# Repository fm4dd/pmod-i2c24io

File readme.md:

## PMOD-I2C24IO

### Description

This project is a 24-bit digital IO expander module, using the Texas Instruments TCA6424A circuit utilizing I2C. The design is available with two connector types: either Type-6 (I2C single-row) or Type-6A (I2C extended double-row) compatible interface per open PMOD interface standard v1.3.1 by Digilent Inc. PMOD (peripheral module interface) standardizes connectivity with FPGA or microcontroller development boards.
This design is registered under the OSHWA Open Source Hardware Self-Certification:  

### Function
In this module, 24 IO pins are controlled through the two-wire serial I2C protocol. For each individual IO pin, a corresponding LED displays its current status with negative logic. A pins logic level '0' lights up the LED, while level '1' turns it off. To fit all IO pins on a reasonably small PMOD, 0402-size SMD components have been selected. DIP switches enable I2C pull-up resistors if needed, and change the I2C bus address between 0x22 and 0x23. Two modules can be chained for a total of 48 IO signals. Three Testpoints can be fitted for I2C bus troubleshooting.  

See also http://fpga.fm4dd.com/

### Schematic

Type-6 v1.1 variant:

Type-6 Physical Dimensions: 60 mm x 20.3 mm

### Hardware Release

|Type     | Version | Gerber | Schema |
|---------|---------|--------|--------|
|Type-6   | 1.0     |[20210906-pmod-i2c24io-t6-gerber-v10.zip](release/t6-v10/20210906-pmod-i2c24io-t6-gerber-v10.zip) | [20210906-pmod-i2c24io-t6-schema-v10.pdf](images/t6-v11/20210906-pmod-i2c24io-t6-schema-v10.pdf) |
|Type-6   |1.1      |[20210919-pmod-i2c24io-t6-gerber-v11.zip](release/t6-v11/20210919-pmod-i2c24io-t6-gerber-v11.zip) | [20210919-pmod-i2c24io-t6-schema-v11.pdf](release/t6-v11/20210919-pmod-i2c24io-t6-schema-v11.pdf)
|Type-6A  |1.1      |[20210919-pmod-i2c24io-t6a-gerber-v11.zip](release/t6a-v11/20210919-pmod-i2c24io-t6a-gerber-v11.zip) | [20210919-pmod-i2c24io-t6a-schema-v11.pdf](release/t6a-v11/20210919-pmod-i2c24io-t6a-schema-v11.pdf)

Type-6A v1.1 variant:

Type-6A Physical Dimensions: 62.5 mm x 21.7 mm

### Module Pin Assignments

Type 6:
| Pin | Signal | Description |
|-----|--------|-------------|
| 1   | Reset  | TCA6424A Reset Pin |
| 2   | Int    | TCA6424A Interrupt Pin |
| 3   | SCL    | I2C Clock Signal |
| 4   | SDA    | I2C Data Signal |
| 5   | GND    | Power Supply Ground |
| 6   | VCC    | Power Supply (3.3V) |

Type 6A (Pin 1-6 same as Type 6)

| Pin | Signal | Description |
|-----|--------|-------------|
| 7   | IO1    | IO signal 1 |
| 8   | IO2    | IO signal 2 |
| 9   | IO3    | IO signal 3 |
| 10  | IO4    | IO signal 4 |
| 11  | GND    | Power Supply Ground |
| 12  | VCC    | Power Supply (3.3V) |

Note: all pin signals are passed from the module pin header to the opposite pin socket, allowing to chain another I2C module to the I2C bus.

#### Rasperry Pi I2C Discovery

First we set Reset pin 'high' to enable circuit operation by exiting the reset state. The gpioset command here is part of the 'gpiod' pin control program and library, installed with 'sudo apt install gpiod'.
```
pi@pi-ms05:~/pmod2rpi/pi-tca6424a $ gpioset gpiochip0 22=1
```
Now we can see the IO expander circuit under address 0x22 (address pin = '1'), or 0x23 (address pin = '0').
```
pi@pi-ms05:~/pmod2rpi/pi-tca6424a $ i2cdetect -y 1
     0  1  2  3  4  5  6  7  8  9  a  b  c  d  e  f
00:          -- -- -- -- -- -- -- -- -- -- -- -- --
10: -- -- -- -- -- -- -- -- -- -- -- -- -- -- -- --
20: -- -- 22 -- -- -- -- -- -- -- -- -- -- -- -- --
...
```

Note: From I2C24IO module hardware version 1.1, two additional 10K pull-up resistors (R28,29) have been fitted to auto-enable the circuit, which eliminates the need to explicitly configure the 'Reset' pin.

### Example Code

| Platform | Folder | Description |
|----------|--------|-------------|
|Raspberry Pi |[pi-tca6424a](examples/pi-tca6424a)   | I2C module driver 'C' program to control the expander 24 IO output pins individually, and as a set |
|Arduino      |[xiao-pmod1-i2c24io](examples/xiao-pmod1-i2c24io)   | Tests I2C ports 0x22 and 0x23. If a module is found, all IO pins are set as 'output=0' (lighting up all LED) |
|Arduino      |[xiao-pmod1-24iodemo](examples/xiao-pmod1-24iodemo)   | Creates a lightshow demo by rotating binary patterns over the 24 IO pins, lighting up connected LEDs |

Two I2C24IO PMOD's connected to the RPi PMOD Interface board connector PMOD1 and PMOD2, running the "xiao-double-i2c24io" example program on the Seeeduino XIAO (Cortex M0):

I2C24IO PMOD connected to the RPi PMOD Interface board connector PMOD4, running the "demotca6424a" example program on the Raspberry Pi:

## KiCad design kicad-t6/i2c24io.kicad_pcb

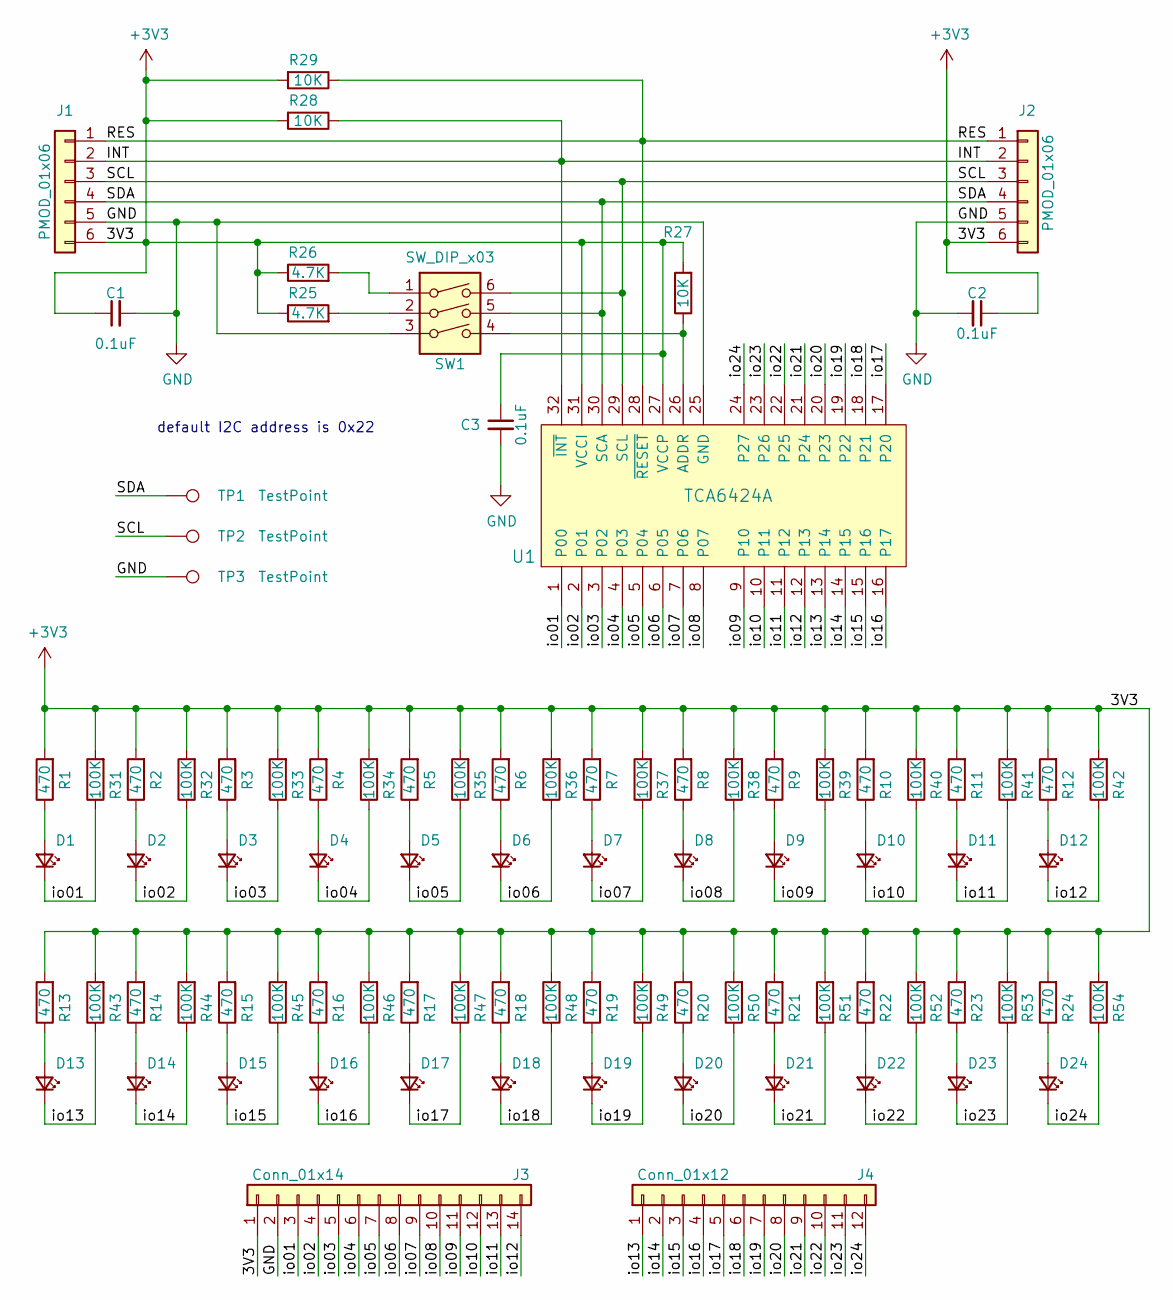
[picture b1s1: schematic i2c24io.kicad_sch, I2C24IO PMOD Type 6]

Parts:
C1, C2, C3: 0.1uF; C_0402_1005Metric
D1, D2, D3, D4, D5, D6, D7, D8, D9, D10, D11, D12, D13, D14, D15, D16, D17, D18, D19, D20, D21, D22, D23, D24: LED_Small; LED_0402_1005Metric
J1: PMOD_01x06; PMOD_Header_1x06_P2.54mm_Horizontal
J2: PMOD_01x06; PMODPinSocket_1x06_P2.54mm_Horizontal
J3: Conn_01x14; PinHeader_1x14_P2.54mm_Vertical
J4: Conn_01x12; PinHeader_1x12_P2.54mm_Vertical
R1, R2, R3, R4, R5, R6, R7, R8, R9, R10, R11, R12, R13, R14, R15, R16, R17, R18, R19, R20, R21, R22, R23, R24: 470; R_0402_1005Metric
R25, R26: 4.7K; R_0402_1005Metric
R27, R28, R29: 10K; R_0402_1005Metric
R31, R32, R33, R34, R35, R36, R37, R38, R39, R40, R41, R42, R43, R44, R45, R46, R47, R48, R49, R50, R51, R52, R53, R54: 100K; R_0402_1005Metric
SW1: SW_DIP_x03; SW_DIP_SPSTx03_Slide_6.7x9.18mm_W7.62mm_P2.54mm_LowProfile
TP1, TP2, TP3: TestPoint; TestPoint_Keystone_5000-5004_Miniature
U1: TCA6424A; VQFN-32-1EP_5x5mm_P0.5mm_EP3.1x3.1mm_ThermalVias

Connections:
+3V3: C1.1, C2.1, C3.1, J1.6, J2.6, J3.1, R1.2, R2.2, R3.2, R4.2, R5.2, R6.2, R7.2, R8.2, R9.2, R10.2, R11.2, R12.2, R13.2, R14.2, R15.2, R16.2, R17.2, R18.2, R19.2, R20.2, R21.2, R22.2, R23.2, R24.2, R25.1, R26.1, R27.2, R28.2, R29.2, R31.2, R32.2, R33.2, R34.2, R35.2, R36.2, R37.2, R38.2, R39.2, R40.2, R41.2, R42.2, R43.2, R44.2, R45.2, R46.2, R47.2, R48.2, R49.2, R50.2, R51.2, R52.2, R53.2, R54.2, U1.27 (VCCP), U1.31 (VCCI)
/INT: J1.2, J2.2, R28.1, U1.32 (~INT)
/RES: J1.1, J2.1, R29.1, U1.28 (~RESET)
/SCL: J1.3, J2.3, SW1.6, TP2.1, U1.29 (SCL)
/SDA: J1.4, J2.4, SW1.5, TP1.1, U1.30 (SCA)
/io01: D1.1 (K), J3.3, R31.1, U1.1 (P00)
/io02: D2.1 (K), J3.4, R32.1, U1.2 (P01)
/io03: D3.1 (K), J3.5, R33.1, U1.3 (P02)
/io04: D4.1 (K), J3.6, R34.1, U1.4 (P03)
/io05: D5.1 (K), J3.7, R35.1, U1.5 (P04)
/io06: D6.1 (K), J3.8, R36.1, U1.6 (P05)
/io07: D7.1 (K), J3.9, R37.1, U1.7 (P06)
/io08: D8.1 (K), J3.10, R38.1, U1.8 (P07)
/io09: D9.1 (K), J3.11, R39.1, U1.9 (P10)
/io10: D10.1 (K), J3.12, R40.1, U1.10 (P11)
/io11: D11.1 (K), J3.13, R41.1, U1.11 (P12)
/io12: D12.1 (K), J3.14, R42.1, U1.12 (P13)
/io13: D13.1 (K), J4.1, R43.1, U1.13 (P14)
/io14: D14.1 (K), J4.2, R44.1, U1.14 (P15)
/io15: D15.1 (K), J4.3, R45.1, U1.15 (P16)
/io16: D16.1 (K), J4.4, R46.1, U1.16 (P17)
/io17: D17.1 (K), J4.5, R47.1, U1.17 (P20)
/io18: D18.1 (K), J4.6, R48.1, U1.18 (P21)
/io19: D19.1 (K), J4.7, R49.1, U1.19 (P22)
/io20: D20.1 (K), J4.8, R50.1, U1.20 (P23)
/io21: D21.1 (K), J4.9, R51.1, U1.21 (P24)
/io22: D22.1 (K), J4.10, R52.1, U1.22 (P25)
/io23: D23.1 (K), J4.11, R53.1, U1.23 (P26)
/io24: D24.1 (K), J4.12, R54.1, U1.24 (P27)
GND: C1.2, C2.2, C3.2, J1.5, J2.5, J3.2, SW1.3, TP3.1, U1.25 (GND)
unnamed: D1.2 (A), R1.1
unnamed: D2.2 (A), R2.1
unnamed: D3.2 (A), R3.1
unnamed: D4.2 (A), R4.1
unnamed: D5.2 (A), R5.1
unnamed: D6.2 (A), R6.1
unnamed: D7.2 (A), R7.1
unnamed: D8.2 (A), R8.1
unnamed: D9.2 (A), R9.1
unnamed: D10.2 (A), R10.1
unnamed: D11.2 (A), R11.1
unnamed: D12.2 (A), R12.1
unnamed: D13.2 (A), R13.1
unnamed: D14.2 (A), R14.1
unnamed: D15.2 (A), R15.1
unnamed: D16.2 (A), R16.1
unnamed: D17.2 (A), R17.1
unnamed: D18.2 (A), R18.1
unnamed: D19.2 (A), R19.1
unnamed: D20.2 (A), R20.1
unnamed: D21.2 (A), R21.1
unnamed: D22.2 (A), R22.1
unnamed: D23.2 (A), R23.1
unnamed: D24.2 (A), R24.1
unnamed: R25.2, SW1.2
unnamed: R26.2, SW1.1
unnamed: R27.1, SW1.4, U1.26 (ADDR)

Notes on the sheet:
default I2C address is 0x22

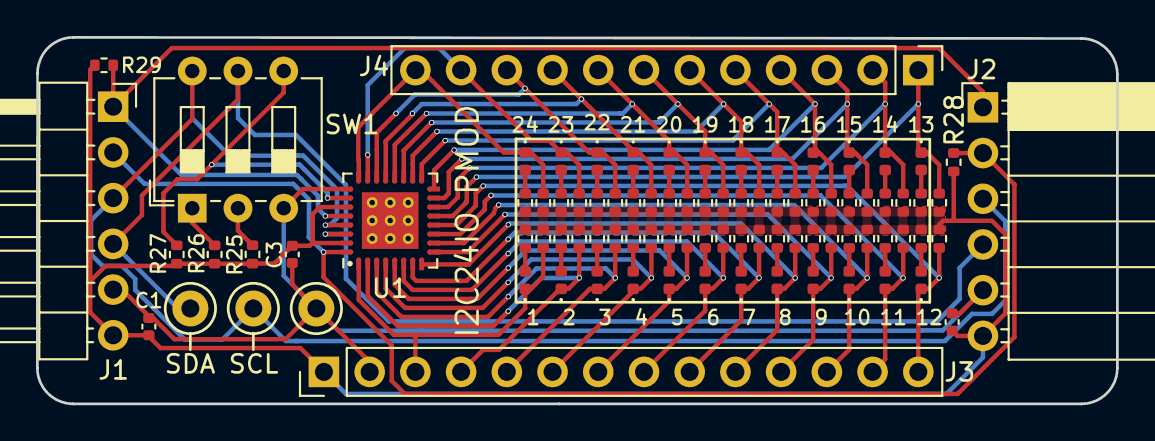
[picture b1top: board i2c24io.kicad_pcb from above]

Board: 2 copper layers, 60.0 x 20.4 mm, 89 parts (0 on the bottom side), 57 nets.

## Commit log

2021-09-24 initial check in
2021-09-25 add demo programi for RPi
2021-09-27 add workflow badges
2021-09-27 add xiao double demo
2021-10-02 add RPi images
2023-11-05 Update rpi.yml
    to manually trigger the workflow
2023-11-05 Update xiao.yml
    to manually trigger the workflow
2023-11-05 KiCad v7 upgrade and GCC v10 fix

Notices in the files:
kicad-t6/i2c24io.kicad_pcb:
License: CC-BY-SA 4.0
